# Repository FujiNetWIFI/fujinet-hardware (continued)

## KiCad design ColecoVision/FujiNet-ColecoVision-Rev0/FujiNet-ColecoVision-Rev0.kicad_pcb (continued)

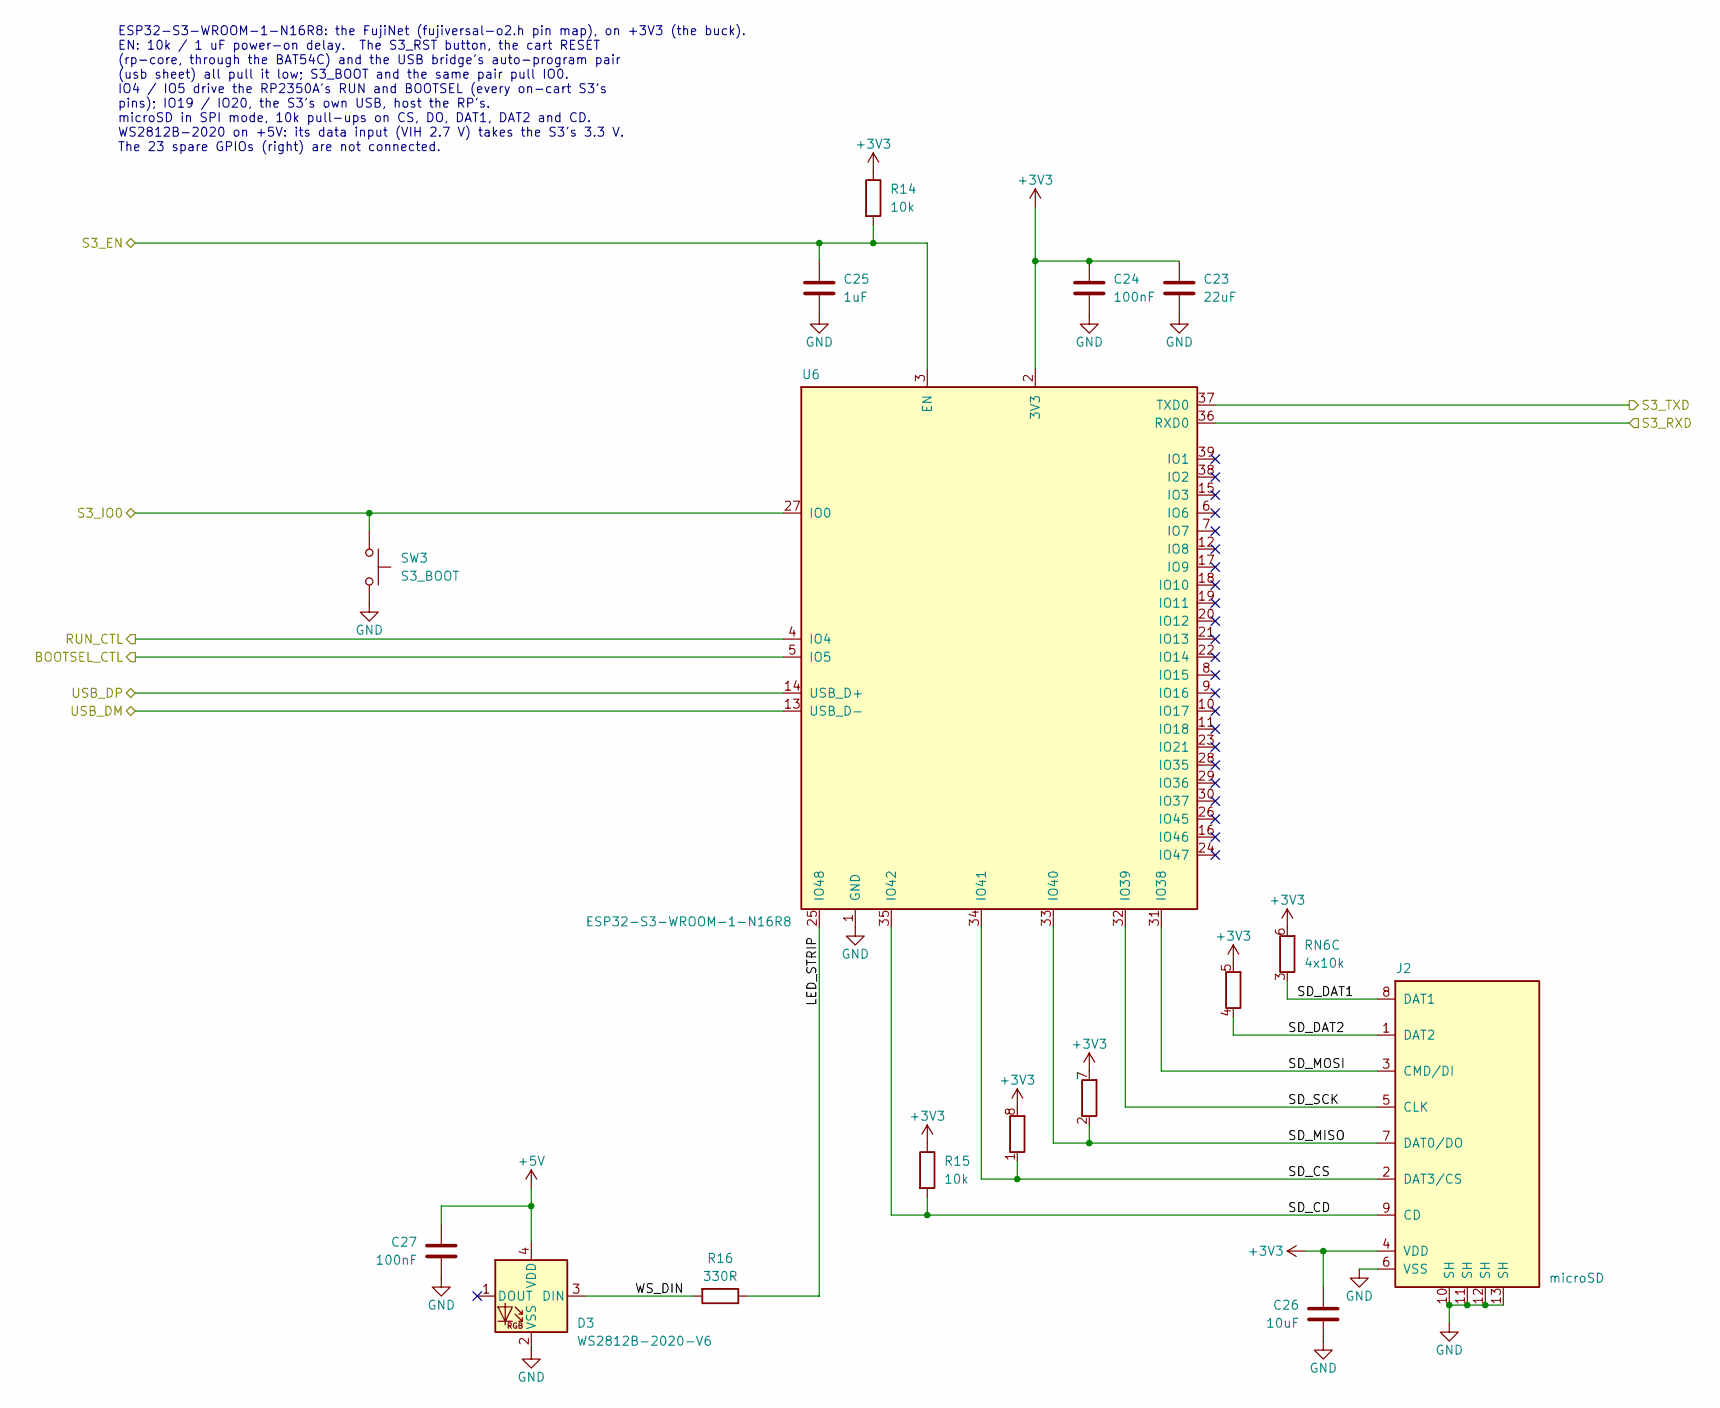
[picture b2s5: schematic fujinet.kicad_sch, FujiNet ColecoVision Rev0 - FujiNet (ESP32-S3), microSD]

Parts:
C23: 22uF; C_0805_2012Metric; MPN CL21A226MAQNNNE; LCSC C45783
C24, C27: 100nF; C_0603_1608Metric; MPN CC0603KRX7R9BB104; LCSC C14663
C25: 1uF; C_0603_1608Metric; MPN CL10A105KB8NNNC; LCSC C15849
C26: 10uF; C_0603_1608Metric; MPN CL10A106KP8NNNC; LCSC C19702
D3: WS2812B-2020-V6; LED_WS2812B-2020_PLCC4_2.0x2.0mm; MPN WS2812B-2020-V6; LCSC C52917434
J2: microSD; TF-SMD_TF-015; MPN TF-015; LCSC C113206
R14, R15: 10k; R_0603_1608Metric; MPN 0603WAF1002T5E; LCSC C25804
R16: 330R; R_0603_1608Metric; MPN 0603WAF3300T5E; LCSC C23138
RN6: 4x10k; R_Array_Convex_4x0603; MPN 4D03WGJ0103T5E; LCSC C29718
SW3: S3_BOOT; SW_SPST_TS-1187A; MPN TS-1187A-B-A-B; LCSC C318884
U6: ESP32-S3-WROOM-1-N16R8; ESP32-S3-WROOM-1; MPN ESP32-S3-WROOM-1-N16R8; LCSC C2913202

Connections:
+3V3: C23.1, C24.1, C26.1, J2.4 (VDD), R14.1, R15.1, RN6.5 (R4.2), RN6.6 (R3.2), RN6.7 (R2.2), RN6.8 (R1.2), U6.2 (3V3); also elsewhere on the board
+5V: C27.1, D3.4 (VDD); also elsewhere on the board
/BOOTSEL_CTL: U6.5 (IO5); also elsewhere on the board
/RUN_CTL: U6.4 (IO4); also elsewhere on the board
/S3_EN: C25.1, R14.2, U6.3 (EN); also elsewhere on the board
/S3_IO0: SW3.1, U6.27 (IO0); also elsewhere on the board
/S3_RXD: U6.36 (RXD0); also elsewhere on the board
/S3_TXD: U6.37 (TXD0); also elsewhere on the board
/USB_DM: U6.13 (USB_D-); also elsewhere on the board
/USB_DP: U6.14 (USB_D+); also elsewhere on the board
/fujinet/LED_STRIP: R16.1, U6.25 (IO48)
/fujinet/SD_CD: J2.9 (CD), R15.2, U6.35 (IO42)
/fujinet/SD_CS: J2.2 (DAT3/CS), RN6.1 (R1.1), U6.34 (IO41)
/fujinet/SD_DAT1: J2.8 (DAT1), RN6.3 (R3.1)
/fujinet/SD_DAT2: J2.1 (DAT2), RN6.4 (R4.1)
/fujinet/SD_MISO: J2.7 (DAT0/DO), RN6.2 (R2.1), U6.33 (IO40)
/fujinet/SD_MOSI: J2.3 (CMD/DI), U6.31 (IO38)
/fujinet/SD_SCK: J2.5 (CLK), U6.32 (IO39)
/fujinet/WS_DIN: D3.3 (DIN), R16.2
GND: C23.2, C24.2, C25.2, C26.2, C27.2, D3.2 (VSS), J2.6 (VSS), J2.10 (SH), J2.11 (SH), J2.12 (SH), J2.13 (SH), SW3.2, U6.1 (GND), U6.40 (GND), U6.41 (GND); also elsewhere on the board

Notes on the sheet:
ESP32-S3-WROOM-1-N16R8: the FujiNet (fujiversal-o2.h pin map), on +3V3 (the buck). EN: 10k / 1 uF power-on delay. The S3_RST button, the cart RESET (rp-core, through the BAT54C) and the USB bridge's auto-program pair (usb sheet) all pull it low; S3_BOOT and the same pair pull IO0. IO4 / IO5 drive t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

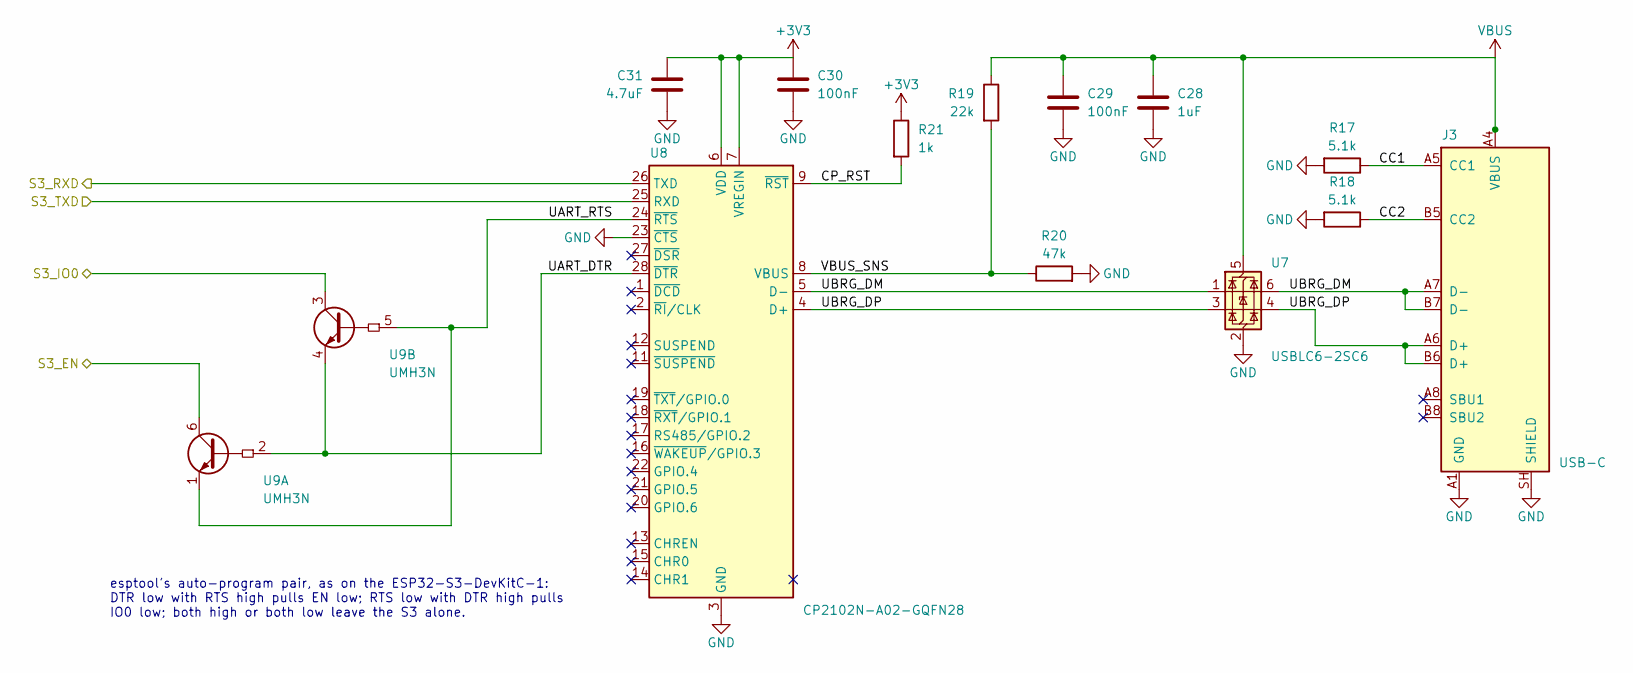
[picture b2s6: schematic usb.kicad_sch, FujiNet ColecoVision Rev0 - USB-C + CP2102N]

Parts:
C28: 1uF; C_0603_1608Metric; MPN CL10A105KB8NNNC; LCSC C15849
C29, C30: 100nF; C_0603_1608Metric; MPN CC0603KRX7R9BB104; LCSC C14663
C31: 4.7uF; C_0603_1608Metric; MPN CL10A475KO8NNNC; LCSC C19666
J3: USB-C; USB_C_Receptacle_HRO_TYPE-C-31-M-12; MPN TYPE-C-31-M-12; LCSC C165948
R17, R18: 5.1k; R_0603_1608Metric; MPN 0603WAF5101T5E; LCSC C23186
R19: 22k; R_0603_1608Metric; MPN 0603WAF2202T5E; LCSC C31850
R20: 47k; R_0603_1608Metric; MPN 0603WAF4702T5E; LCSC C25819
R21: 1k; R_0603_1608Metric; MPN 0603WAF1001T5E; LCSC C21190
U7: USBLC6-2SC6; SOT-23-6; MPN USBLC6-2SC6; LCSC C7519
U8: CP2102N-A02-GQFN28; QFN-28-1EP_5x5mm_P0.5mm_EP3.35x3.35mm; MPN CP2102N-A02-GQFN28R; LCSC C964632
U9: UMH3N; SOT-363_SC-70-6; MPN UMH3N; LCSC C62892

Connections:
+3V3: C30.1, C31.1, R21.1, U8.6 (VDD), U8.7 (VREGIN); also elsewhere on the board
/S3_EN: U9.6 (C1); also elsewhere on the board
/S3_IO0: U9.3 (C2); also elsewhere on the board
/S3_RXD: U8.26 (TXD); also elsewhere on the board
/S3_TXD: U8.25 (RXD); also elsewhere on the board
/usb/CC1: J3.A5 (CC1), R17.1
/usb/CC2: J3.B5 (CC2), R18.1
/usb/CP_RST: R21.2, U8.9 (~RST)
/usb/UART_DTR: U8.28 (~DTR), U9.2 (B1), U9.4 (E2)
/usb/UART_RTS: U8.24 (~RTS), U9.1 (E1), U9.5 (B2)
/usb/UBRG_DM: J3.A7 (D-), J3.B7 (D-), U7.1 (I/O1), U7.6 (I/O1), U8.5 (D-)
/usb/UBRG_DP: J3.A6 (D+), J3.B6 (D+), U7.3 (I/O2), U7.4 (I/O2), U8.4 (D+)
/usb/VBUS_SNS: R19.2, R20.1, U8.8 (VBUS)
GND: C28.2, C29.2, C30.2, C31.2, J3.A1 (GND), J3.A12 (GND), J3.B1 (GND), J3.B12 (GND), J3.SH (SHIELD), R17.2, R18.2, R20.2, U7.2 (GND), U8.3 (GND), U8.23 (~CTS), U8.29 (GND); also elsewhere on the board
VBUS: C28.1, C29.1, J3.A4 (VBUS), J3.A9 (VBUS), J3.B4 (VBUS), J3.B9 (VBUS), R19.1, U7.5 (VBUS); also elsewhere on the board

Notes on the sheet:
esptool's auto-program pair, as on the ESP32-S3-DevKitC-1: DTR low with RTS high pulls EN low; RTS low with DTR high pulls IO0 low; both high or both low leave the S3 alone.

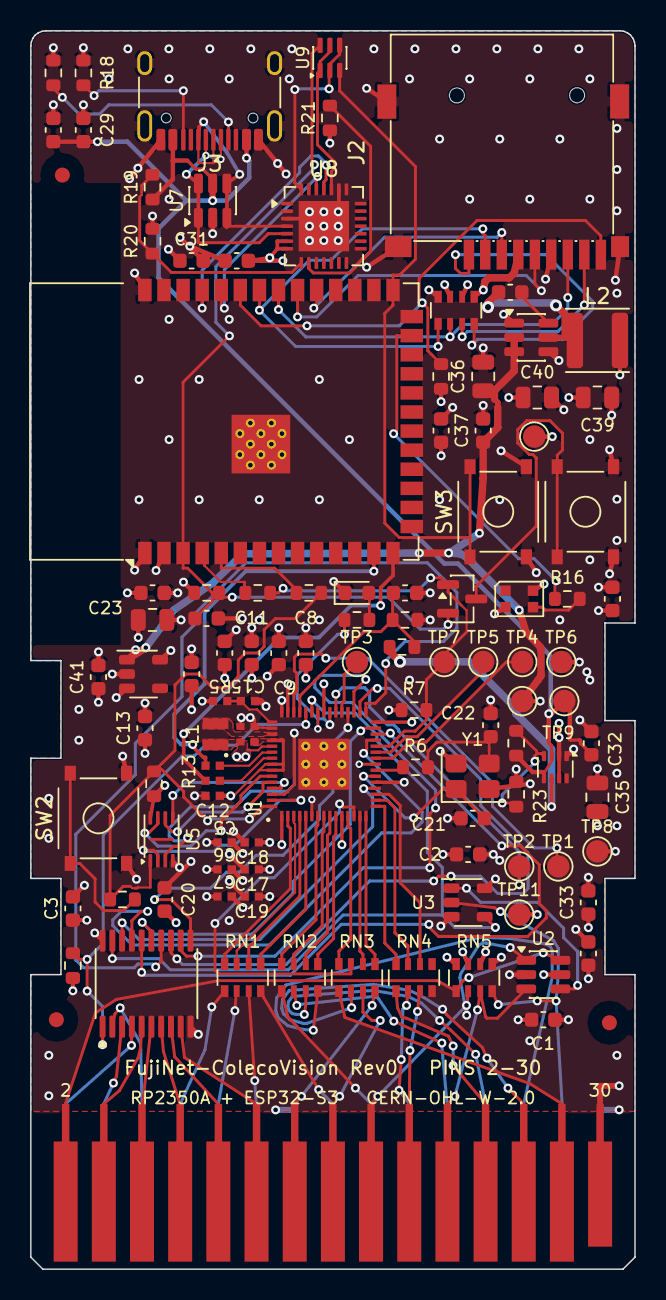
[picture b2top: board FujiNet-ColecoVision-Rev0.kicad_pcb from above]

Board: 4 copper layers, 40.2 x 82.4 mm, 110 parts (0 on the bottom side), 112 nets.

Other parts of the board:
FID1, FID2, FID3: Fiducial_1mm_Mask2mm

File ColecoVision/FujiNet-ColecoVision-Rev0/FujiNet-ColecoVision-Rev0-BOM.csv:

Qty,References,Value,Footprint,MPN,Manufacturer,LCSC,Description,Notes
16,C1 C2 C3 C4 C8 C9 C10 C11 C20 C24 C27 C29 C30 C34 C37 C38,100nF,C_0603_1608Metric,CC0603KRX7R9BB104,YAGEO,C14663,capacitor (several uses: see schematic),
6,C5 C6 C7 C12 C17 C18,100nF,RPI_C0402,CL05B104KO5NNNC,Samsung Electro-Mechanics,C1525,capacitor (several uses: see schematic),
3,C13 C26 C33,10uF,C_0603_1608Metric,CL10A106KP8NNNC,Samsung Electro-Mechanics,C19702,capacitor (several uses: see schematic),
2,C14 C16,4.7uF,RPI_C0402_wide,CL05A475MP5NRNC,Samsung Electro-Mechanics,C23733,capacitor (several uses: see schematic),
2,C15 C19,4.7uF,RPI_C0402,CL05A475MP5NRNC,Samsung Electro-Mechanics,C23733,capacitor (several uses: see schematic),
2,C21 C22,15pF,C_0603_1608Metric,CL10C150JB8NNNC,Samsung Electro-Mechanics,C1644,crystal load,
5,C23 C35 C36 C39 C40,22uF,C_0805_2012Metric,CL21A226MAQNNNE,Samsung Electro-Mechanics,C45783,capacitor (several uses: see schematic),
5,C25 C28 C32 C41 C42,1uF,C_0603_1608Metric,CL10A105KB8NNNC,Samsung Electro-Mechanics,C15849,capacitor (several uses: see schematic),
1,C31,4.7uF,C_0603_1608Metric,CL10A475KO8NNNC,Samsung Electro-Mechanics,C19666,CP2102N VDD bulk,
1,D1,red,LED_0603_1608Metric,KT-0603R,Hubei KENTO Elec,C2286,RP activity LED (GP25),
1,D2,BAT54C,SOT-23,"BAT54C,215",Nexperia,C37704,"RESET steering, common cathode",
1,D3,WS2812B-2020-V6,LED_WS2812B-2020_PLCC4_2.0x2.0mm,WS2812B-2020-V6,Worldsemi,C52917434,status LED on +5V (datasheet VDD 3.7-5.3 V; VIH 2.7 V takes 3.3 V data),
1,J1,Coleco_Cart_Edge_30,Coleco_Cart_Edge_30,,,,"ColecoVision cartridge edge, 2x15 gold fingers, 2.54 mm pitch; odd pins on the back, even pins on the component face",not in BOM
1,J2,microSD,TF-SMD_TF-015,TF-015,SOFNG,C113206,"microSD push-push, SPI mode",
1,J3,USB-C,USB_C_Receptacle_HRO_TYPE-C-31-M-12,TYPE-C-31-M-12,Korean Hroparts Elec,C165948,power + S3 programming / console,
1,L1,3.3uH,RPI_L_AOTA-B201610S3R3,AOTA-B201610S3R3-101-T,Abracon,C42411119,RP2350 core SMPS inductor (polarity marked),
1,L2,6.8uH,L_Sunlord_SWPA4030S,SWPA4030S6R8MT,Sunlord,C62684,buck inductor,
7,R1 R3 R7 R9 R14 R15 R23,10k,R_0603_1608Metric,0603WAF1002T5E,UNI-ROYAL,C25804,resistor (several uses: see schematic),
1,R2,680R,R_0603_1608Metric,0603WAF6800T5E,UNI-ROYAL,C23228,LED series (~2 mA),
1,R4,15k,R_0603_1608Metric,0603WAF1502T5E,UNI-ROYAL,C22809,console 5V sense divider (0.6 x CONS_5V),
1,R5,33R,RPI_R0402,0402WGF330JTCE,UNI-ROYAL,C25105,VREG_AVDD RC filter (R_FILT),
5,R6 R8 R10 R11 R21,1k,R_0603_1608Metric,0603WAF1001T5E,UNI-ROYAL,C21190,resistor (several uses: see schematic),
2,R12 R13,27R,RPI_R0402,0402WGF270JTCE,UNI-ROYAL,C25100,USB series,
1,R16,330R,R_0603_1608Metric,0603WAF3300T5E,UNI-ROYAL,C23138,WS2812 data series,
2,R17 R18,5.1k,R_0603_1608Metric,0603WAF5101T5E,UNI-ROYAL,C23186,UFP Rd,
1,R19,22k,R_0603_1608Metric,0603WAF2202T5E,UNI-ROYAL,C31850,VBUS sense divider,
1,R20,47k,R_0603_1608Metric,0603WAF4702T5E,UNI-ROYAL,C25819,VBUS sense divider,
1,R22,33k,R_0603_1608Metric,0603WAF3302T5E,UNI-ROYAL,C4216,mux priority threshold (VBUS > 4.3 V),
4,RN1 RN2 RN3 RN4,4x330R,R_Array_Convex_4x0603,4D03WGJ0331T5E,UNI-ROYAL,C12018,RN (several uses: see schematic),
2,RN5 RN6,4x10k,R_Array_Convex_4x0603,4D03WGJ0103T5E,UNI-ROYAL,C29718,RN (several uses: see schematic),
1,SW1,RESET,SW_SPST_TS-1187A,TS-1187A-B-A-B,XKB Connection,C318884,cart RESET: RP RUN + S3 EN through the BAT54C,
1,SW2,BOOTSEL,SW_SPST_TS-1187A,TS-1187A-B-A-B,XKB Connection,C318884,RP2350A BOOTSEL (hold while pressing RESET),
1,SW3,S3_BOOT,SW_SPST_TS-1187A,TS-1187A-B-A-B,XKB Connection,C318884,ESP32-S3 BOOT (IO0),
1,TP1,SELFTEST,TestPoint_Pad_D1.5mm,,,,"test pad: GP29, a self-test trigger for bring-up",not in BOM
1,TP2,DBG_TX,TestPoint_Pad_D1.5mm,,,,"test pad: GP24 (UART1 TX), debug UART (3.3 V)",not in BOM
1,TP3,GP23,TestPoint_Pad_D1.5mm,,,,"test pad: GP23, spare",not in BOM
1,TP4,SWCLK,TestPoint_Pad_D1.5mm,,,,test pad,not in BOM
1,TP5,SWDIO,TestPoint_Pad_D1.5mm,,,,test pad,not in BOM
1,TP6,GND,TestPoint_Pad_D1.5mm,,,,test pad,not in BOM
1,TP7,RUN,TestPoint_Pad_D1.5mm,,,,test pad,not in BOM
1,TP8,CONS_5V,TestPoint_Pad_D1.5mm,,,,bring-up pad: console 5V (edge pin 30),not in BOM
1,TP9,VBUS,TestPoint_Pad_D1.5mm,,,,bring-up pad: USB VBUS,not in BOM
1,TP10,+5V,TestPoint_Pad_D1.5mm,,,,bring-up pad: +5V (mux output),not in BOM
1,TP11,+3V3_RP,TestPoint_Pad_D1.5mm,,,,bring-up pad: +3V3_RP (RP LDO),not in BOM
1,TP12,+3V3,TestPoint_Pad_D1.5mm,,,,bring-up pad: +3V3 (buck: S3 side),not in BOM
1,U1,RP2350A,RPI_RP2350A_QFN60,RP2350A,Raspberry Pi,C42411118,RP2350A: serves the ColecoVision cart bus (fujicoleco),
1,U2,74LVC1G11,SOT-23-6,SN74LVC1G11DBVR,Texas Instruments,C22046,select AND: /8000 . /A000 . /C000,
1,U3,74LVC1G08,SOT-23-5,SN74LVC1G08DBVR,Texas Instruments,C7666,select AND: . /E000 = /CE (GP26 and the buffer /OE),
1,U4,74LVC245A,TSSOP-20_4.4x6.5mm_P0.65mm,SN74LVC245APWR,Texas Instruments,C7848,"data buffer, 5V-tolerant at 3.3V: edge D0-D7 <-> GP15-22",
1,U5,W25Q16JVUXIQ,Winbond_USON-8-1EP_3x2mm_P0.5mm_EP0.2x1.6mm,W25Q16JVUXIQ,Winbond,C2843335,2 MB QSPI boot flash,
1,U6,ESP32-S3-WROOM-1-N16R8,ESP32-S3-WROOM-1,ESP32-S3-WROOM-1-N16R8,Espressif,C2913202,FujiNet core (fujiversal-coleco),
1,U7,USBLC6-2SC6,SOT-23-6,USBLC6-2SC6,STMicroelectronics,C7519,"USB ESD: D+, D-, VBUS",
1,U8,CP2102N-A02-GQFN28,QFN-28-1EP_5x5mm_P0.5mm_EP3.35x3.35mm,CP2102N-A02-GQFN28R,Silicon Labs,C964632,USB-UART for S3 flashing/console (self-powered),
1,U9,UMH3N,SOT-363_SC-70-6,UMH3N,Jiangsu Changjing (JSCJ),C62892,esptool auto-program (DevKitC-1 style),
1,U10,TPS2116,SOT-583-8,TPS2116DRLR,Texas Instruments,C3235557,"power mux: VBUS first, console 5V second",
1,U11,AP63203WU,TSOT-23-6,AP63203WU-7,Diodes Incorporated,C780769,"3.3V 2A buck (S3, SD, CP2102N)",
1,U12,AP2112K-3.3,SOT-23-5,AP2112K-3.3TRG1,Diodes Incorporated,C51118,"RP2350A 3.3V LDO (IOVDD, VREG_VIN, VREG_AVDD, flash, bus logic), 600mA, fast start",
1,Y1,12MHz,Crystal_SMD_3225-4Pin_3.2x2.5mm,ABM8-272-T3,Abracon,C20625731,RP2350 12 MHz crystal,

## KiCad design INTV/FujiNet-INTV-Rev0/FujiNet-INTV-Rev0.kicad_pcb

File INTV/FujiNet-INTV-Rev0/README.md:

# FujiNet-INTV Rev0

All-in-one **Intellivision FujiNet cartridge**: one board carrying both halves of the
INTV FujiNet stack —

- **RP2354A** (RP2350A + 2 MB stacked flash, QFN-60) running the
  [Minty](https://github.com/gtortone/Minty)-derived cartridge firmware from
  `fujinet-firmware/pico/intellivision/firmware`, built with `-DPICO_BOARD=fujicard`.
  It emulates the cartridge on the CP-1610 bus (GPIO0–15 = AD0–AD15 wired **directly**
  to the 5 V cart edge — RP2350-family pads are 5 V-tolerant with IOVDD = 3.3 V) and
  exposes the FujiNet mailbox at `$9C00-$9F3F`.
- **ESP32-S3-WROOM-1-N16R8** running the `fujiversal-intv` build of
  [fujinet-firmware](https://github.com/FujiNetWIFI/fujinet-firmware)
  (`./build.sh -e fujiversal-intv`). The two MCUs are linked **on-board over native
  USB** — the S3 is the USB *host* (GPIO19/20) and the RP2354A is a CDC-ACM *device*
  (VID 0xCafe), exactly as the firmware expects. No UART link exists between them.

A **single USB-C port** replicates the ESP32-S3-DevKitC-1 v1.1 "UART" port:
CP2102N-A02-GQFN28 bridge into UART0 (GPIO43/44) with the classic DTR/RTS → EN/IO0
auto-program circuit (UMH3NTN dual transistor), so `pio run -t upload` just works.

## Provenance & license

This design **adapts the [PiNTY CARD](https://oshwlab.com/yannick.erb/intv-pirto-hb)**
by Yannick Erb (with gtortone), licensed **CERN-OHL-W-2.0**. The 44-pin edge-finger
geometry, the direct-connect CP-1610 bus interface, the RP2354A support circuit
(crystal, VREG inductor, USB series resistors) and the ECS-audio RC network follow the
PiNTY CARD design; the full bus/edge net map was verified by tracing the published
PiNTY gerbers. This derivative is likewise released under **CERN-OHL-W-2.0**.

The outline, the left shell notch and the two shell-post holes follow Andrea Ottaviani's
**[PiRTO II](https://github.com/aotta/PiRTOII)** (GPL-3.0), so the board fits a PiRTO II
shell. Dimensions only: no file from it is in this repository.

Additional sources: standard package footprints from the official KiCad footprint
library (CC-BY-SA 4.0 with the KiCad libraries exception); microSD footprint reused
from `Coco/CoCo-FujiNet-Rev0000` in this repository; USB-UART port per the public
Espressif ESP32-S3-DevKitC-1 v1.1 reference schematic.

## Status — Rev0, schematic + placed board, **unrouted**

- ERC: 0 errors / 0 warnings. DRC (with `--schematic-parity`): 0 electrical errors;
  remaining items are the expected *unconnected* (unrouted) markers and a handful of
  silkscreen-text overlap warnings to tidy while routing.
- Every net was machine-checked against the firmware pin maps
  (`pico/intellivision/firmware/boards/fujicard.h` and
  `include/pinmap/fujiversal-intv.h`) and the PiNTY-verified edge map — 100/100 checks.
- **Routing is the next step** (interactive, in KiCad ≥ 10): suggested stackup
  F.Cu / In1.Cu (GND plane) / In2.Cu (3V3 + 5 V/VIN islands) / B.Cu, 1.6 mm.
  Route the AD0–15 fan-out from U1 straight down to the fingers, keep the
  USB_DP/USB_DM pair (U1 ↔ U2) short and coupled (90 Ω target, `USB_DIFF` net class),
  then pour GND on In1 and both outer layers.

## Board facts

| | |
|---|---|
| Outline | 58.2 × 78.0 mm, PiRTO-II-profile shell fit: bottom tongue with 45° chamfers, left shell notch, two Ø5.38 mm shell-post holes |
| Edge | 2×22 fingers, 2.54 mm pitch, 1.32 × 7.0 mm pads, copper held 0.9 mm off the edge (per PiNTY) |
| ESP32 antenna | module **overhangs the top edge by ~5.7 mm** so the RF keepout falls off-board (Espressif best practice) — the cart shell needs a matching relief |
| USB-C / microSD | both exit through the top edge; the USB-C (J3 at y 75.2) has its shell face 0.45 mm past the edge, HRO's recommended PCB-edge position (moved 1.8 mm on 2026-10-13: at y 77 the face sat 1.35 mm inside, where a plug's overmold meets the PCB edge) |
| Power | cart +5 V (edge 43) ⊕ USB VBUS → SS34 OR → 470 µF → AP63203 3.3 V/2 A buck → both MCUs. Estimated draw ~80 mA avg / ~400 mA peak (WiFi bursts) |
| ECS audio | GPIO28 → R5 1k / C18 1 µF → edge pin 6, **DNP** (firmware `CONFIG_ECS_AUDIO=OFF`); fit R5/C18 to enable once firmware supports it |

## Flashing

- **ESP32-S3**: the USB-C port (CP2102N + auto-program). `upload_port` is the
  CP2102N's `/dev/ttyUSB*`.
- **RP2354A**: no dedicated port — it is flashed *through* the ESP32-S3 over the
  internal USB link: normal path is the mailbox BOOTSEL doorbell
  (`FUJI_MB_BOOTSEL_DOORBELL`, magic `0xB5` → `reset_usb_boot()`); recovery path is
  hardware forcing (S3 GPIO5 → Q3 pulls QSPI_SS low, S3 GPIO4 → Q2 pulses RUN).
  The S3-side PICOBOOT client currently lives on the `intv-combined-flash` branch of
  fujinet-firmware. Manual fallback: SW2 (BOOTSEL) + SW1 (RUN) — but note BOOTSEL
  enumerates to the *S3*, not to a PC. Last resort: SWD pads TP1/TP2/TP3 on the back.
- Note: the `fujicard` pico build target is not yet in
  `pico/intellivision/firmware/scripts/build-*.sh` / CI — build it directly with
  `cmake -B build -DPICO_BOARD=fujicard -DCMAKE_BUILD_TYPE=Release -DCONFIG_FUJINET=ON`.

## Fabrication notes

- 4-layer, 1.6 mm, ENIG (or selective **hard gold on the edge fingers**), **30–45°
  edge bevel** on the finger edge. Fingers intentionally stop 0.9 mm short of the
  edge so the bevel does not cut copper.
- Min through-hole on this board is 0.2 mm (ESP32 module thermal vias) — confirm with
  the fab or convert those to 0.3 mm.
- Copper-to-edge clearance is set to 0 in the board file (edge fingers demand it);
  keep normal clearances elsewhere when routing.
- BOM: `FujiNet-INTV-Rev0-BOM.csv` (MPN/LCSC filled where verified — complete the
  remaining generic passives at order time).

## Bring-up checklist (bench items that cannot be verified in CAD)

1. Measure console 5 V rail headroom under WiFi-burst load on each console variant
   before trusting cart-only power (USB-C can co-power on the bench).
2. Scope the 5 V-tolerance precondition: IOVDD (3.3 V) must be up before the console
   drives the bus — MSYNC gating covers normal operation; verify power-up ordering.
3. WS2812B-2020 runs from the diode-OR'd rail (~4.7 V): VDD spec is 3.5–5.3 V and the
   3.3 V data level is marginal at higher VDD — verify, or fit a small series diode
   drop if flickery.
4. WiFi RF check: USB-C and microSD metal bodies sit ~5 mm laterally from the antenna
   (which overhangs the board edge). Verify RSSI is acceptable in-shell; Rev1 could
   move the module if needed.
5. Shell fit: antenna + USB-C overhang need shell relief; verify the left notch and
   post holes against the actual PiRTO-II-style shell before ordering many boards.
6. Test hardware BOOTSEL forcing (drive GPIO5 low, pulse GPIO4) before trusting the
   PICOBOOT reflash path.

## Files

- `FujiNet-INTV-Rev0.kicad_pro / .kicad_sch / *.kicad_sch / .kicad_pcb` — KiCad 10
  project (root + 4 sheets: cart-rp2354a, esp32s3-sd, usb-uart, power)
- `FujiNet-INTV.kicad_sym`, `FujiNet-INTV.pretty/` — fully self-contained project
  libraries (no external library dependencies)
- `FujiNet-INTV-Rev0-BOM.csv` — grouped BOM with DNP column
- `docs/` — schematic PDF, layout SVGs, 3D renders

PCBs can be ordered by submitting gerbers exported from the routed board to the fab
house of your choice (routing pass required first).

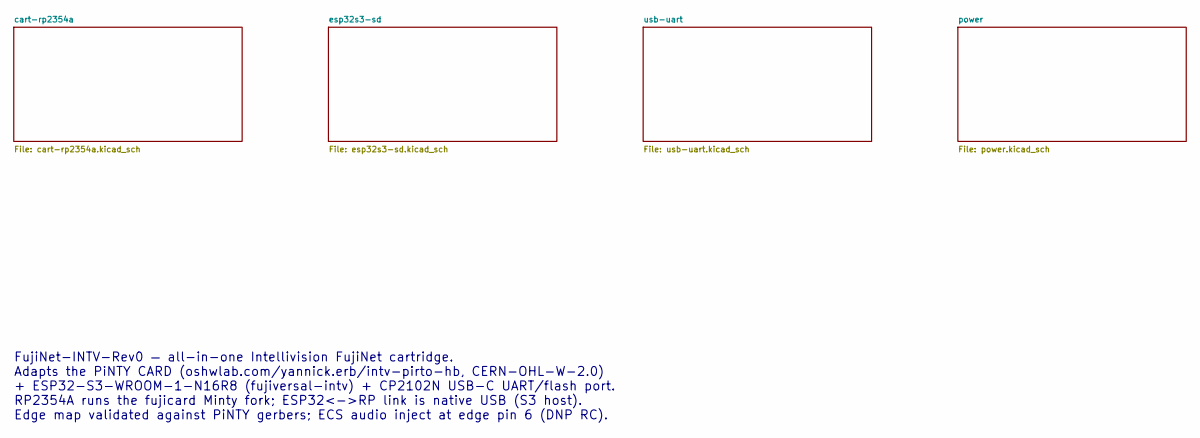
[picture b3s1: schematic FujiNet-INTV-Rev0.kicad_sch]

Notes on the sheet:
FujiNet-INTV-Rev0 — all-in-one Intellivision FujiNet cartridge. Adapts the PiNTY CARD (oshwlab.com/yannick.erb/intv-pirto-hb, CERN-OHL-W-2.0) + ESP32-S3-WROOM-1-N16R8 (fujiversal-intv) + CP2102N USB-C UART/flash port. RP2354A runs the fujicard Minty fork; ESP32<->RP link is native USB (S3 host). Ed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

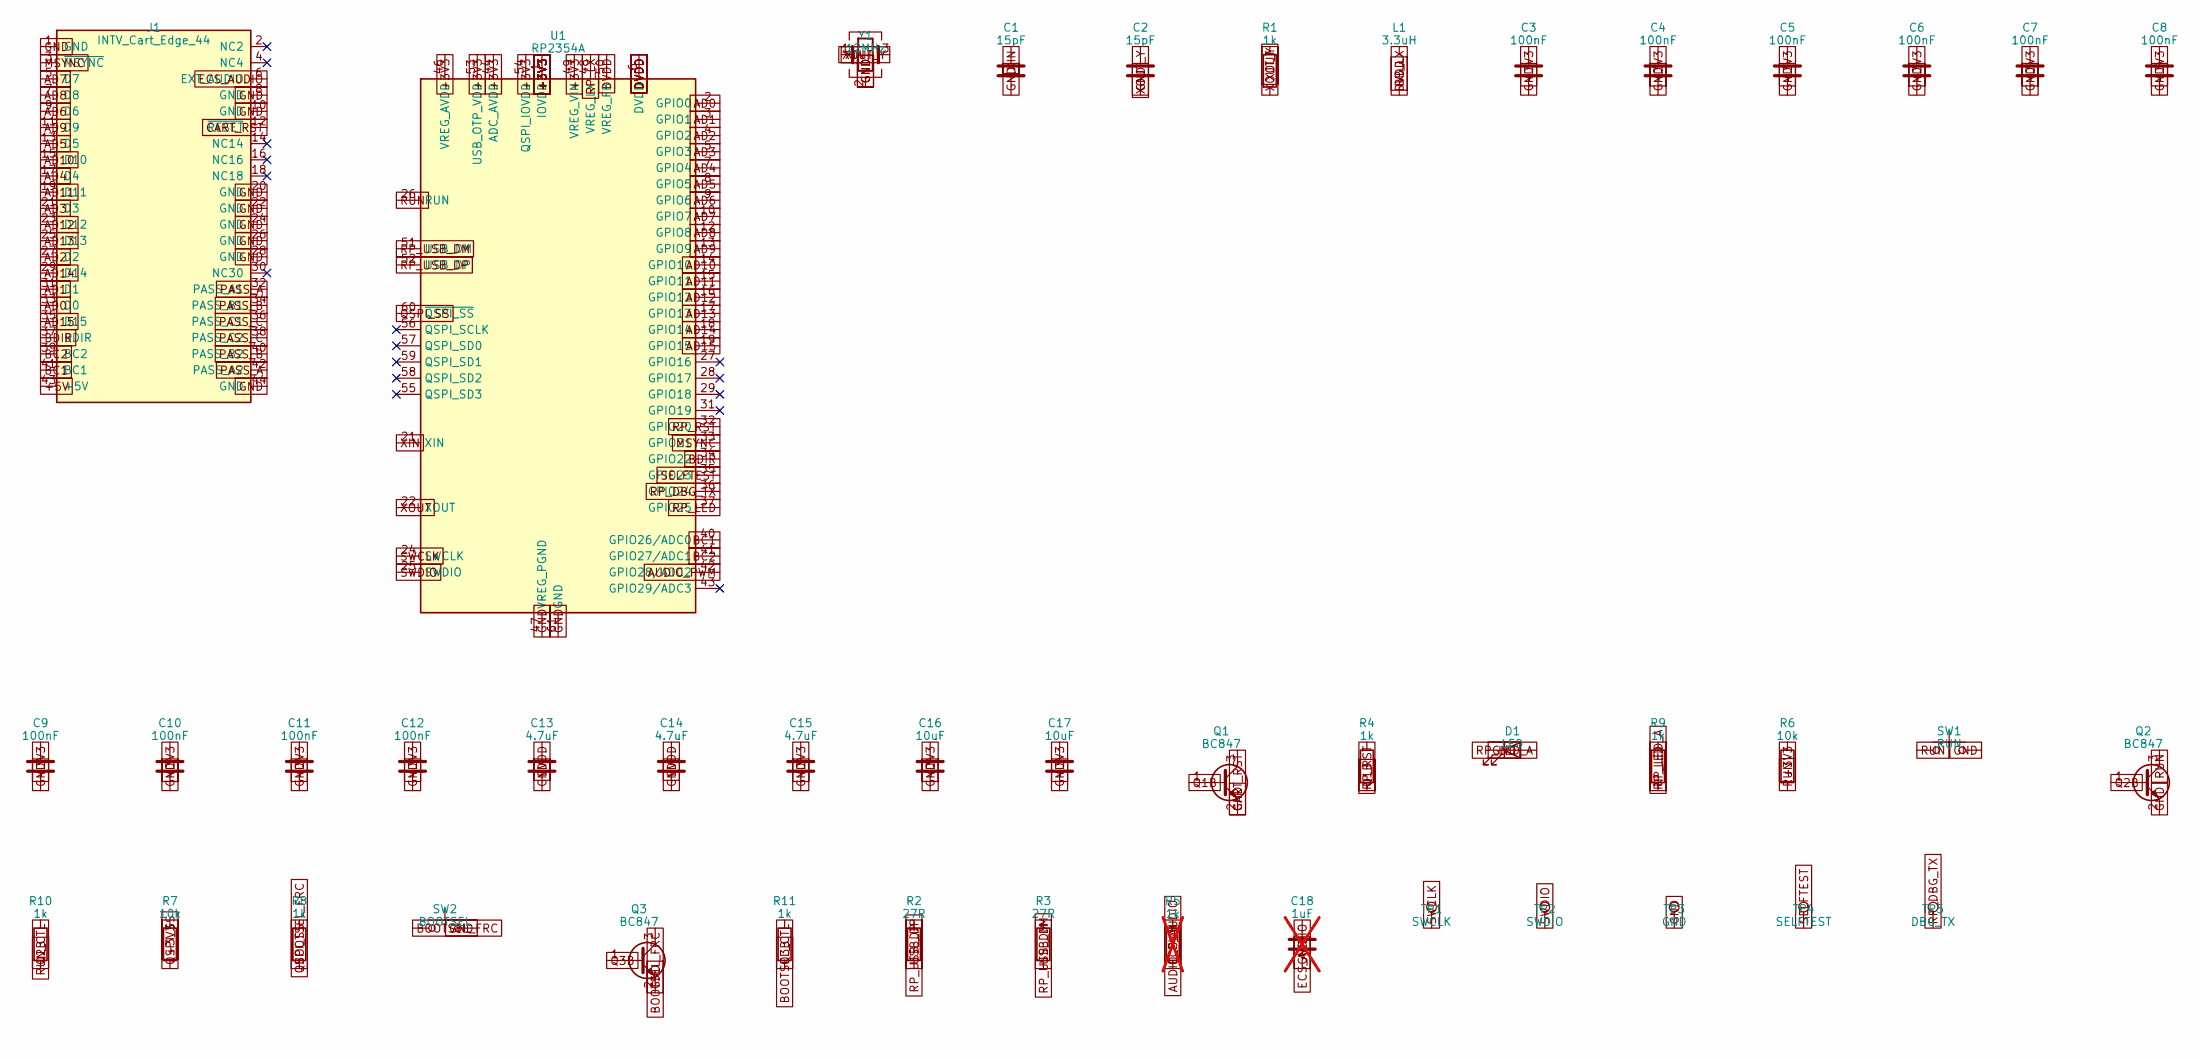
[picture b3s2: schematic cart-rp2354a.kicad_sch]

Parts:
C1, C2: 15pF; C_0603_1608Metric
C3, C4, C5, C6, C7, C8, C9, C10, C11, C12: 100nF; C_0603_1608Metric
C13, C14, C15: 4.7uF; C_0603_1608Metric
C16, C17: 10uF; C_0603_1608Metric; LCSC C19702
C18: 1uF; C_0603_1608Metric; not fitted
D1: LED; LED_0603_1608Metric
J1: INTV_Cart_Edge_44; MPN card edge, 2x22, 2.54mm
L1: 3.3uH; L_2016Metric; MPN AOTA-B201610S3R3-101-T; LCSC C42411119
Q1, Q2, Q3: BC847; SOT-23; LCSC C8598
R1, R4, R8, R9, R10, R11: 1k; R_0603_1608Metric
R2, R3: 27R; R_0603_1608Metric
R5: 1k; R_0603_1608Metric; not fitted
R6, R7: 10k; R_0603_1608Metric
SW1: RUN; SW_SPST_TL3342
SW2: BOOTSEL; SW_SPST_TL3342
TP1: SWCLK; TestPoint_Pad_D1.5mm
TP2: SWDIO; TestPoint_Pad_D1.5mm
TP3: GND; TestPoint_Pad_D1.5mm
TP4: SELFTEST; TestPoint_Pad_D1.5mm
TP5: DBG_TX; TestPoint_Pad_D1.5mm
U1: RP2354A; QFN-60-1EP_7x7mm_P0.4mm_EP3.4x3.4mm; MPN RP2354A; LCSC C41378174
Y1: 12MHz; Crystal_SMD_3225-4Pin_3.2x2.5mm; MPN ABM8-272-T3; LCSC C20625731

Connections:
+3V3: C3.1, C4.1, C5.1, C6.1, C7.1, C8.1, C9.1, C10.1, C11.1, C12.1, C15.1, C16.1, C17.1, R6.1, R7.1, U1.1 (IOVDD), U1.11 (IOVDD), U1.20 (IOVDD), U1.30 (IOVDD), U1.38 (IOVDD), U1.44 (ADC_AVDD), U1.45 (IOVDD), U1.46 (VREG_AVDD), U1.49 (VREG_VIN), U1.53 (USB_OTP_VDD), U1.54 (QSPI_IOVDD); also elsewhere on the board
+5V: J1.43 (+5V); also elsewhere on the board
AD0: J1.33 (D0), U1.2 (GPIO0)
AD1: J1.31 (D1), U1.3 (GPIO1)
AD2: J1.27 (D2), U1.4 (GPIO2)
AD3: J1.21 (D3), U1.5 (GPIO3)
AD4: J1.17 (D4), U1.7 (GPIO4)
AD5: J1.13 (D5), U1.8 (GPIO5)
AD6: J1.9 (D6), U1.9 (GPIO6)
AD7: J1.5 (D7), U1.10 (GPIO7)
AD8: J1.7 (D8), U1.12 (GPIO8)
AD9: J1.11 (D9), U1.13 (GPIO9)
AD10: J1.15 (D10), U1.14 (GPIO10)
AD11: J1.19 (D11), U1.15 (GPIO11)
AD12: J1.23 (D12), U1.16 (GPIO12)
AD13: J1.25 (D13), U1.17 (GPIO13)
AD14: J1.29 (D14), U1.18 (GPIO14)
AD15: J1.35 (D15), U1.19 (GPIO15)
AUDIO_PWM: R5.1, U1.42 (GPIO28/ADC2)
BC1: J1.41 (BC1), U1.40 (GPIO26/ADC0)
BC2: J1.39 (BC2), U1.41 (GPIO27/ADC1)
BDIR: J1.37 (BDIR), U1.34 (GPIO22)
BOOTSEL_CTL: R11.1; also elsewhere on the board
BOOTSEL_FRC: Q3.3 (C), R8.2, SW2.1
CART_RST: J1.12 (~RESET), Q1.3 (C)
DVDD: C13.1, C14.1, L1.2, U1.6 (DVDD), U1.23 (DVDD), U1.39 (DVDD), U1.50 (VREG_FB)
ECS_AUDIO: C18.1, J1.6 (EXT_AUDIO), R5.2
GND: C1.2, C2.2, C3.2, C4.2, C5.2, C6.2, C7.2, C8.2, C9.2, C10.2, C11.2, C12.2, C13.2, C14.2, C15.2, C16.2, C17.2, C18.2, D1.1 (K), J1.1 (GND), J1.8 (GND), J1.10 (GND), J1.20 (GND), J1.22 (GND), J1.24 (GND), J1.26 (GND), J1.28 (GND), J1.44 (GND), Q1.2 (E), Q2.2 (E), Q3.2 (E), SW1.2, SW2.2, TP3.1, U1.47 (VREG_PGND), U1.61 (GND), Y1.2 (G), Y1.4 (G); also elsewhere on the board
MSYNC: J1.3 (~MSYNC), U1.33 (GPIO21)
PASS_A: J1.32 (PASS_A1), J1.42 (PASS_A2)
PASS_B: J1.34 (PASS_B1), J1.40 (PASS_B2)
PASS_C: J1.36 (PASS_C1), J1.38 (PASS_C2)
Q1B: Q1.1 (B), R4.2
Q2B: Q2.1 (B), R10.2
Q3B: Q3.1 (B), R11.2
QSPI_SS: R7.2, R8.1, U1.60 (~QSPI_SS)
RP_DBG_TX: TP5.1, U1.36 (GPIO24)
RP_LED: R9.1, U1.37 (GPIO25)
RP_LED_A: D1.2 (A), R9.2
RP_LX: L1.1, U1.48 (VREG_LX)
RP_RST: R4.1, U1.32 (GPIO20)
RP_USB_DM: R3.1, U1.51 (USB_DM)
RP_USB_DP: R2.1, U1.52 (USB_DP)
RUN: Q2.3 (C), R6.2, SW1.1, U1.26 (RUN)
RUN_CTL: R10.1; also elsewhere on the board
SELFTEST: TP4.1, U1.35 (GPIO23)
SWCLK: TP1.1, U1.24 (SWCLK)
SWDIO: TP2.1, U1.25 (SWDIO)
USB_DM: R3.2; also elsewhere on the board
USB_DP: R2.2; also elsewhere on the board
XIN: C1.1, U1.21 (XIN), Y1.1
XOUT: R1.1, U1.22 (XOUT)
XOUT_Y: C2.1, R1.2, Y1.3

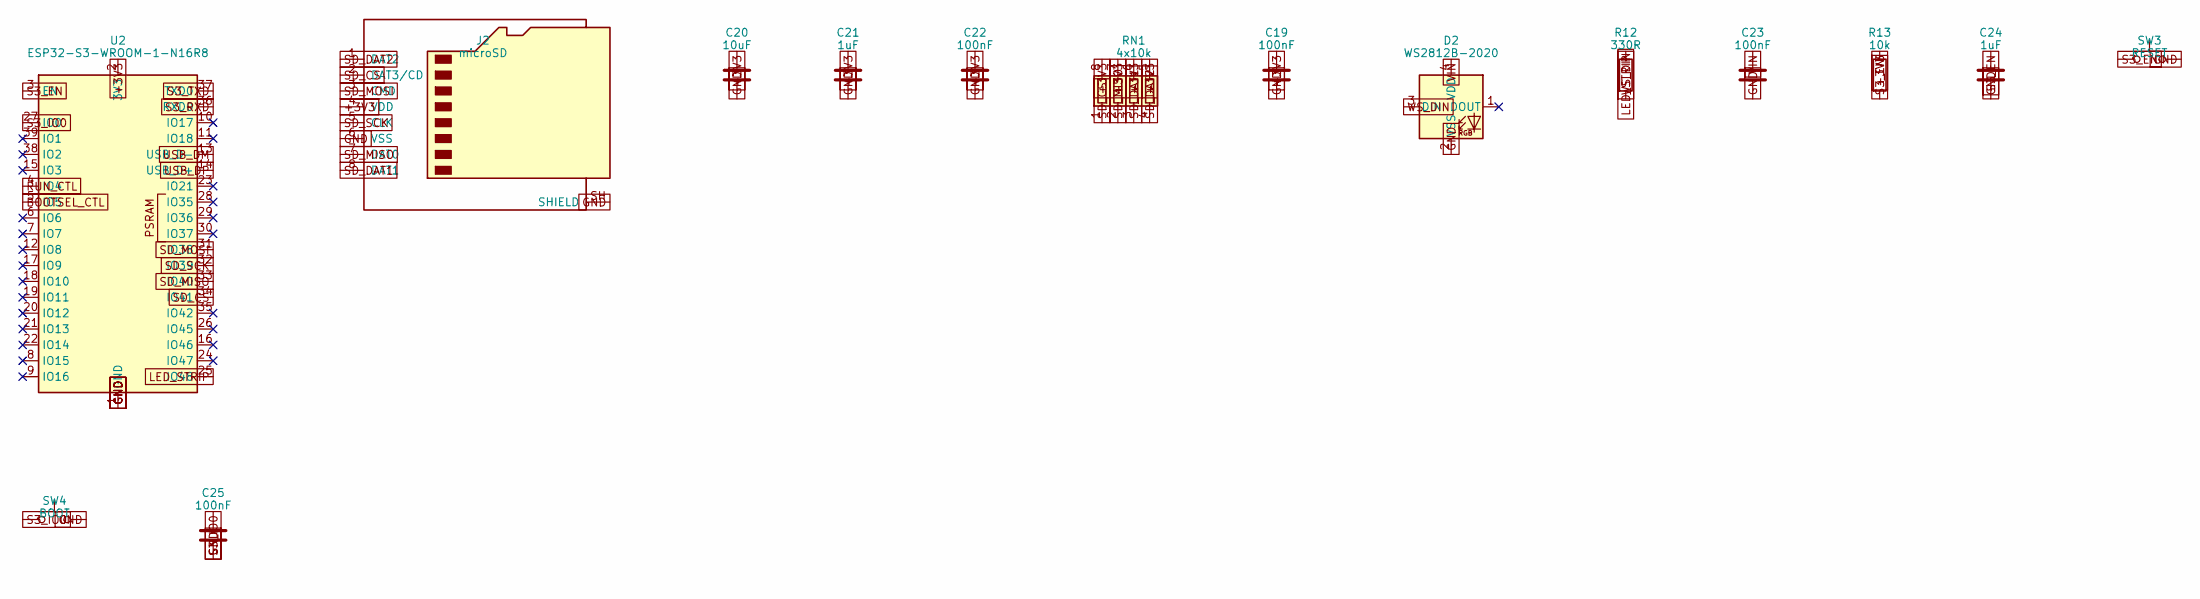
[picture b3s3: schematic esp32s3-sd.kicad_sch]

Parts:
C19, C22, C23, C25: 100nF; C_0603_1608Metric
C20: 10uF; C_0603_1608Metric; LCSC C19702
C21, C24: 1uF; C_0603_1608Metric
D2: WS2812B-2020; LED_WS2812B-2020_PLCC4_2.0x2.0mm; MPN WS2812B-2020; LCSC C5149201
J2: microSD; microSD_SUNTECH_ST-TF-003A; MPN SUNTECH ST-TF-003A
R12: 330R; R_0603_1608Metric
R13: 10k; R_0603_1608Metric
RN1: 4x10k; R_Array_Convex_4x0603
SW3: RESET; SW_SPST_TL3342
SW4: BOOT; SW_SPST_TL3342
U2: ESP32-S3-WROOM-1-N16R8; ESP32-S3-WROOM-1; MPN ESP32-S3-WROOM-1-N16R8; LCSC C2913202

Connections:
+3V3: C19.1, C20.1, C21.1, C22.1, J2.4 (VDD), R13.1, RN1.5 (R4.2), RN1.6 (R3.2), RN1.7 (R2.2), RN1.8 (R1.2), U2.2 (3V3); also elsewhere on the board
BOOTSEL_CTL: U2.5 (IO5); also elsewhere on the board
GND: C19.2, C20.2, C21.2, C22.2, C23.2, C24.2, C25.2, D2.2 (VSS), J2.6 (VSS), J2.SH (SHIELD), SW3.2, SW4.2, U2.1 (GND), U2.40 (GND), U2.41 (GND); also elsewhere on the board
LED_STRIP: R12.1, U2.25 (IO48)
RUN_CTL: U2.4 (IO4); also elsewhere on the board
S3_EN: C24.1, R13.2, SW3.1, U2.3 (EN); also elsewhere on the board
S3_IO0: C25.1, SW4.1, U2.27 (IO0); also elsewhere on the board
S3_RXD: U2.36 (RXD0); also elsewhere on the board
S3_TXD: U2.37 (TXD0); also elsewhere on the board
SD_CS: J2.2 (DAT3/CD), RN1.1 (R1.1), U2.34 (IO41)
SD_DAT1: J2.8 (DAT1), RN1.3 (R3.1)
SD_DAT2: J2.1 (DAT2), RN1.4 (R4.1)
SD_MISO: J2.7 (DAT0), RN1.2 (R2.1), U2.33 (IO40)
SD_MOSI: J2.3 (CMD), U2.31 (IO38)
SD_SCK: J2.5 (CLK), U2.32 (IO39)
USB_DM: U2.13 (USB_D-); also elsewhere on the board
USB_DP: U2.14 (USB_D+); also elsewhere on the board
VIN: C23.1, D2.4 (VDD); also elsewhere on the board
WS_DIN: D2.3 (DIN), R12.2

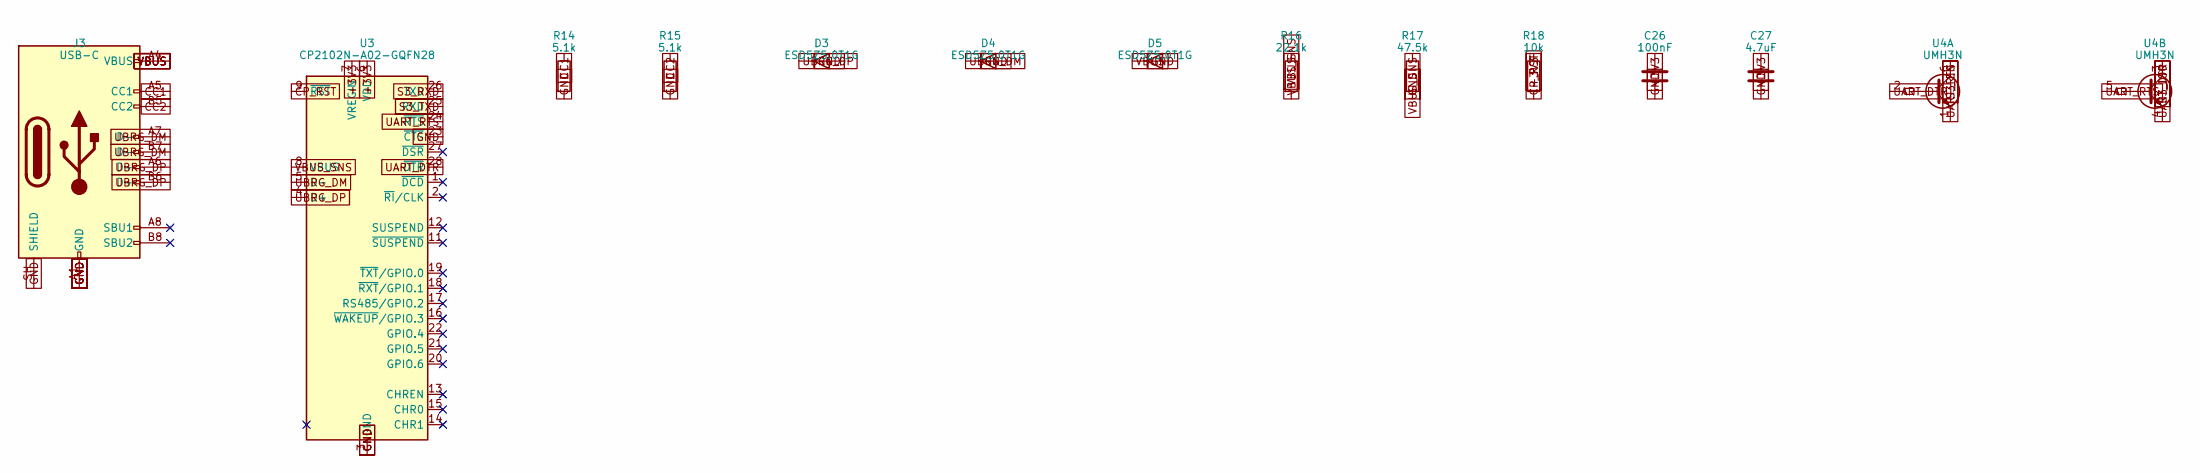
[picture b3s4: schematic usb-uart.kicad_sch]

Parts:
C26: 100nF; C_0603_1608Metric
C27: 4.7uF; C_0603_1608Metric
D3, D4, D5: ESD5Z5.0T1G; D_SOD-523; LCSC C316061
J3: USB-C; USB_C_Receptacle_HRO_TYPE-C-31-M-12; MPN HRO TYPE-C-31-M-12; LCSC C5178539
R14, R15: 5.1k; R_0603_1608Metric
R16: 22.1k; R_0603_1608Metric
R17: 47.5k; R_0603_1608Metric
R18: 10k; R_0603_1608Metric
U3: CP2102N-A02-GQFN28; QFN-28-1EP_5x5mm_P0.5mm_EP3.35x3.35mm; MPN CP2102N-A02-GQFN28R
U4: UMH3N; SOT-363_SC-70-6; LCSC C123008

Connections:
+3V3: C26.1, C27.1, R18.1, U3.6 (VDD), U3.7 (VREGIN); also elsewhere on the board
CC1: J3.A5 (CC1), R14.1
CC2: J3.B5 (CC2), R15.1
CP_RST: R18.2, U3.9 (~RST)
GND: C26.2, C27.2, D3.2 (A), D4.2 (A), D5.2 (A), J3.A1 (GND), J3.A12 (GND), J3.B1 (GND), J3.B12 (GND), J3.SH (SHIELD), R14.2, R15.2, R17.2, U3.3 (GND), U3.23 (~CTS), U3.29 (GND); also elsewhere on the board
S3_EN: U4.6 (C1); also elsewhere on the board
S3_IO0: U4.3 (C2); also elsewhere on the board
S3_RXD: U3.26 (TXD); also elsewhere on the board
S3_TXD: U3.25 (RXD); also elsewhere on the board
UART_DTR: U3.28 (~DTR), U4.2 (B1), U4.4 (E2)
UART_RTS: U3.24 (~RTS), U4.1 (E1), U4.5 (B2)
UBRG_DM: D4.1 (K), J3.A7 (D-), J3.B7 (D-), U3.5 (D-)
UBRG_DP: D3.1 (K), J3.A6 (D+), J3.B6 (D+), U3.4 (D+)
VBUS: D5.1 (K), J3.A4 (VBUS), J3.A9 (VBUS), J3.B4 (VBUS), J3.B9 (VBUS), R16.1; also elsewhere on the board
VBUS_SNS: R16.2, R17.1, U3.8 (VBUS)
